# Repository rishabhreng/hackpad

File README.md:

# MacroPad Overview

A 6-key macropad, in an "A" shape, with a 0.91" OLED display and a rotary encoder. It also has one LED under the central key, and everything is controlled with KMK firmware.

This was my first time designing a macropad or any other  electronics with KiCad, and I really enjoyed it (esp. learning more about the wiring). Fortunately, I have some experience with CAD in Onshape, so modeling the case went smoothly.

|          |      |
|----------|------|
|  |  |

## Pictures

| Schematic | PCB | Case |
|:-:|:-:|:-:|
|  |  |  |

**Schematic** and **PCB** designed in _KiCad_. The **CAD** model and whole assembly were designed in _Onshape_ (after trying this process in Fusion 360, I wanted to redesign in Onshape as it felt much more natural and familiar).

## Bill of Materials (BOM)

- 1x XIAO RP2040
- 6x MX-like switches
- 6x DSA keycaps
- 6x through-hole 1N4148 diodes
- 1x SK6812 MINI-E LED
- 1x 0.91" 128x32 OLED display
- 1x EC11E rotary encoder
- 1x case, made of 2 printed parts ([Top.step](production/top.step) and [Bottom.step](production/bottom.step) )
- 4x M3x16mm screws

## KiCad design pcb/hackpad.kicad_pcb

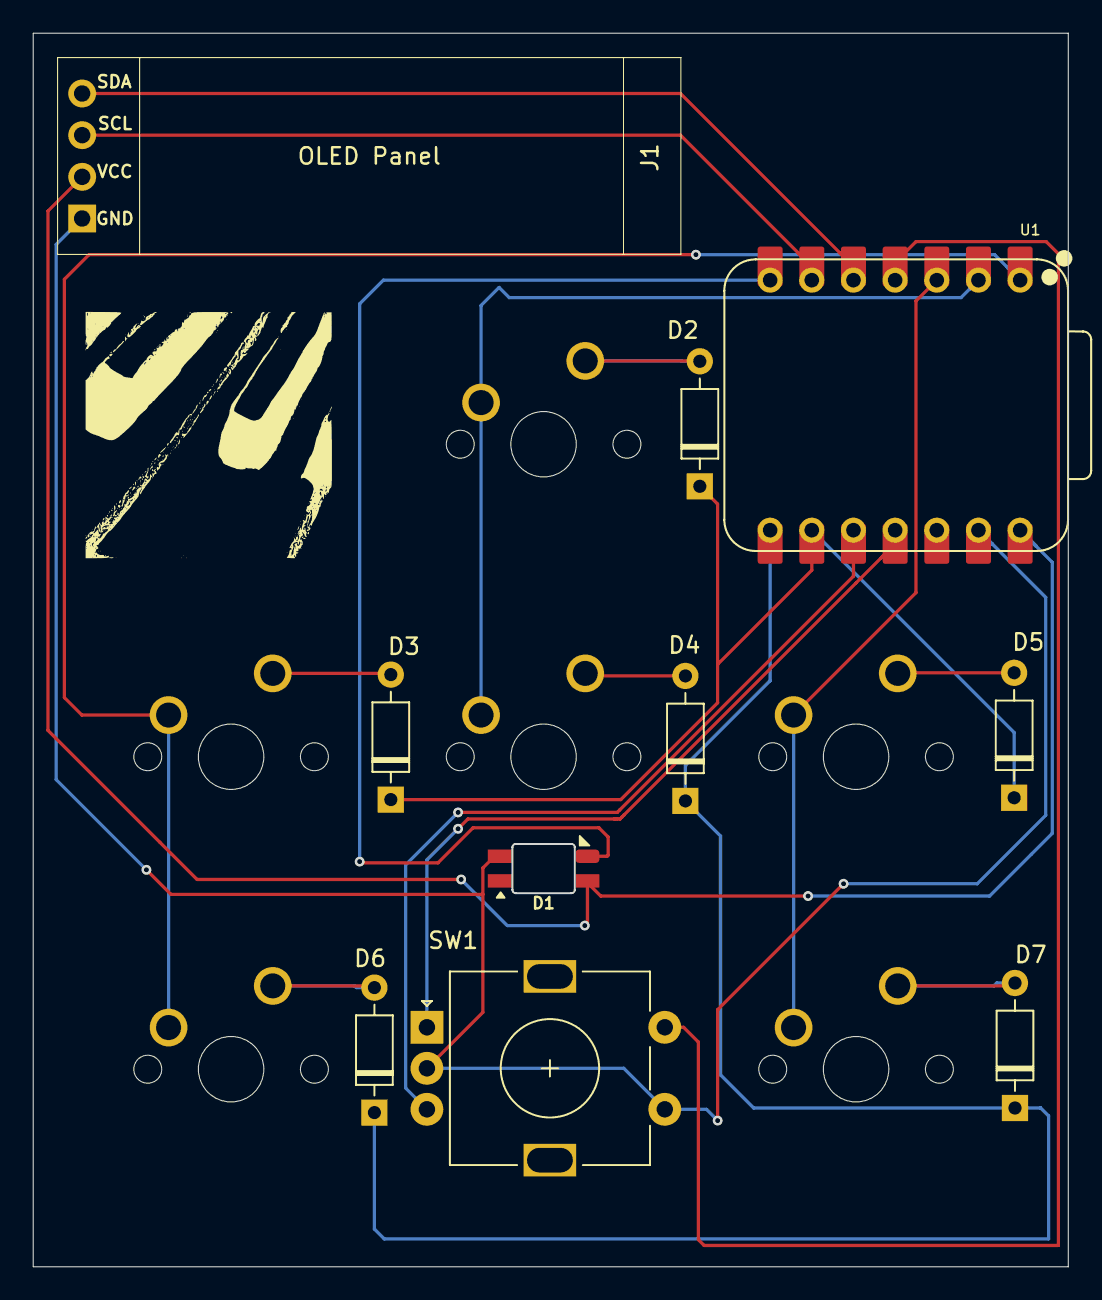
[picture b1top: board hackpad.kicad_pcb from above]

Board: 2 copper layers, 63.1 x 75.2 mm, 16 parts (0 on the bottom side), 19 nets.

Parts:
D1: SK6812MINI; SK6812-MINI-E
D2, D3, D4, D5, D6, D7: D; D_DO-35_SOD27_P7.62mm_Horizontal
J1: OLED DISPLAY; SSD1306-0.91-OLED-4pin-128x32
SW1: RotaryEncoder_Switch; RotaryEncoder_Alps_EC11E-Switch_Vertical_H20mm
SW2, SW3, SW4, SW5, SW6, SW7: SW_Push; MX-Solderable-1U
U1: XIAO-RP2040-DIP

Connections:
COL1: SW3.1, SW6.1, U1.1 (GPIO26/ADC0/A0)
COL2: SW2.1, SW4.1, U1.2 (GPIO27/ADC1/A1)
COL3: SW5.1, SW7.1, U1.3 (GPIO28/ADC2/A2)
GND: D1.2 (VSS), J1.1, SW1.C, SW1.S1, U1.13 (GND)
LED: D1.3 (DIN), U1.7 (GPIO0/TX)
unnamed: D2.2 (A), SW2.2
unnamed: D3.2 (A), SW3.2
unnamed: D4.2 (A), SW4.2
unnamed: D5.2 (A), SW5.2
unnamed: D6.2 (A), SW6.2
unnamed: D7.2 (A), SW7.2
ROW1: D2.1 (K), D3.1 (K), D5.1 (K), U1.9 (GPIO2/SCK)
ROW2: D4.1 (K), D6.1 (K), D7.1 (K), U1.8 (GPIO1/RX)
R_A: SW1.A, U1.11 (GPIO3/MOSI)
R_B: SW1.B, U1.10 (GPIO4/MISO)
R_SW: SW1.S2, U1.4 (GPIO29/ADC3/A3)
SCL: J1.3, U1.6 (GPIO7/SCL)
SDA: J1.4, U1.5 (GPIO6/SDA)
VCC: D1.4 (VDD), J1.2, U1.14 (VBUS)
